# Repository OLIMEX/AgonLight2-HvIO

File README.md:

# AgonLight2-HvIO
High voltage optoisolated Four outputs and Four inputs and two Temperature sensor connectors for AgonLight2

https://www.olimex.com/Products/Retro-Computers/AgonLight2-HvIO/open-source-hardware

Features:

* AgonLight GPIO connector
* Four SSR relays 240VAC 1A
* Four optoisolated inputs 120-240VAC
* Two Dallas18B20 temperature sensors
* LED output indicators
* LED input indicators
* Power supply 3.3V and 5V LED indicators
* Dimensions 100x70mm

## Licenses

* Hardware is released under CERN Open Hardware Licence Version 2 - Strongly Reciprocal, all silkscreen credits to Olimex should remain;
* Software is released under GPL3 Licensee
* Documentation is released under CC BY-SA 4.0

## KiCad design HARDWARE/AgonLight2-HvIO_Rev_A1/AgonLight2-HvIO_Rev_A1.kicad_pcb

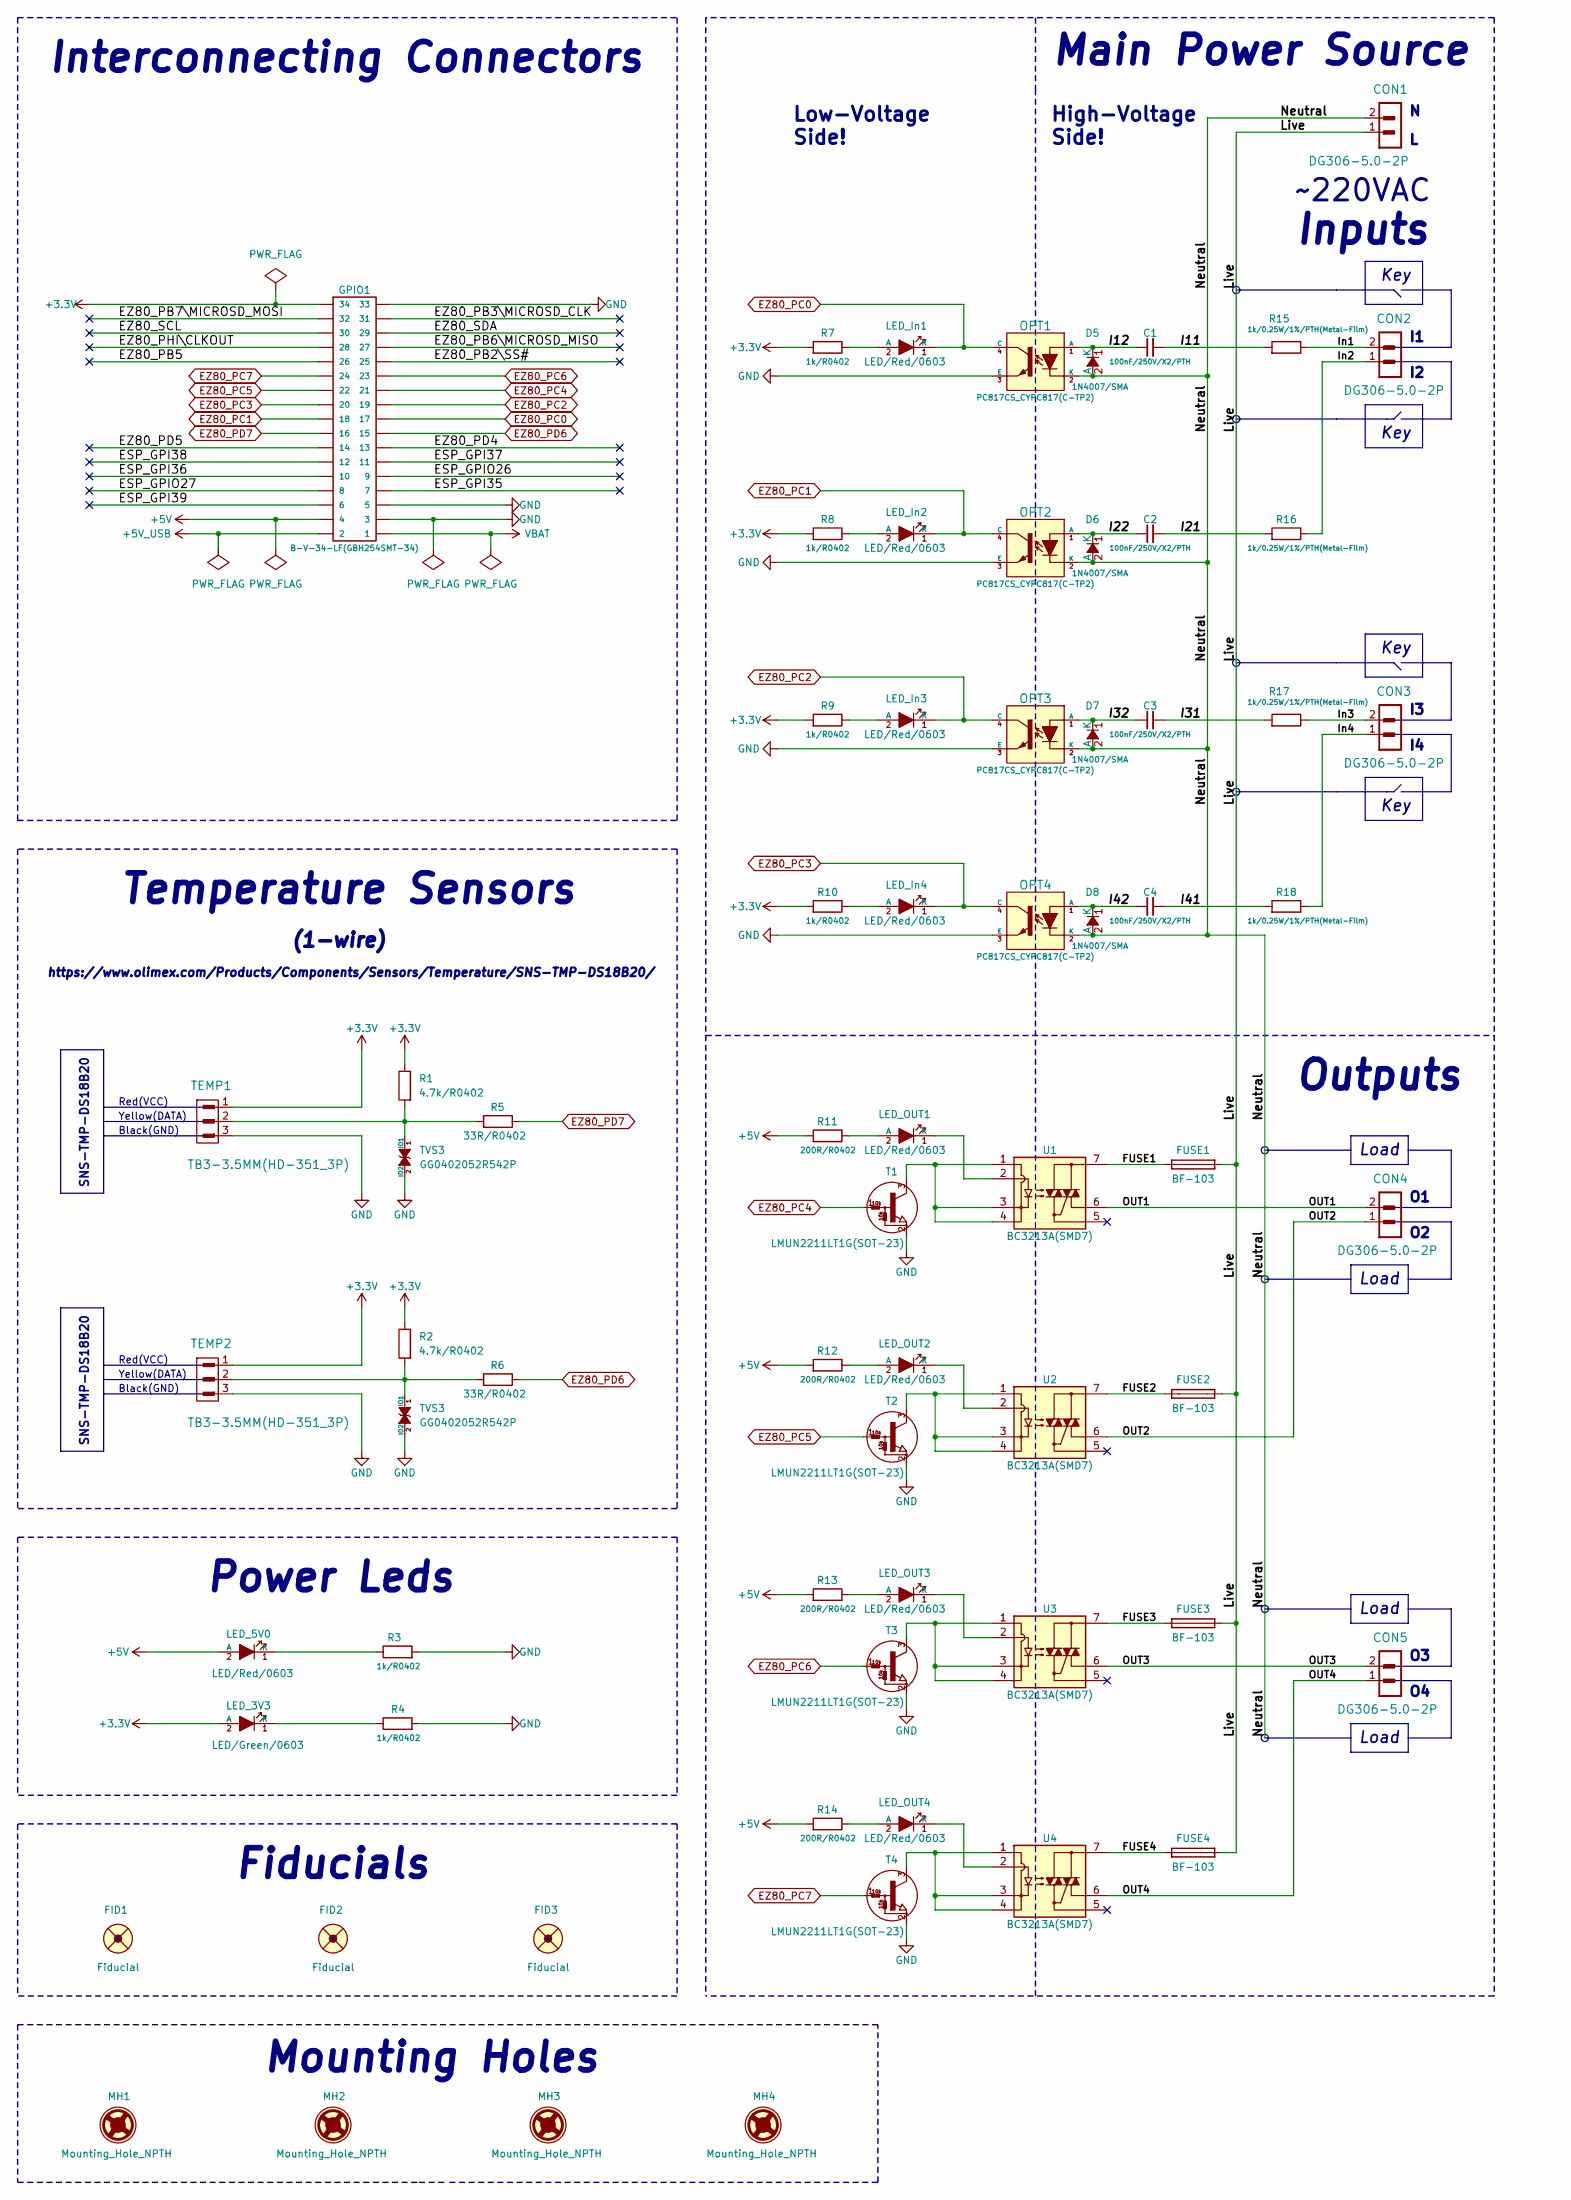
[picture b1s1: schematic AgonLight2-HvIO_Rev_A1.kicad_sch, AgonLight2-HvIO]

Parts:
C1, C2, C3, C4: 100nF/250V/X2/PTH; C600-700x250mils
CON1, CON2, CON3, CON4, CON5: DG306-5.0-2P; TB2-DG306-5.0_2P
D5, D6, D7, D8: 1N4007/SMA; SMA-KA
FID1, FID2, FID3: Fiducial; Fiducial1x3
FUSE1, FUSE2, FUSE3, FUSE4: BF-103; FUSE-HOLDER_BF-103
GPIO1: B-V-34-LF(GBH254SMT-34); GBH-254-SMT-34
LED_3V3: LED/Green/0603; LED_0603_KA
LED_5V0: LED/Red/0603; LED_0603_KA
LED_In1, LED_In2, LED_In3, LED_In4: LED/Red/0603; LED_0603_KA
LED_OUT1, LED_OUT2, LED_OUT3, LED_OUT4: LED/Red/0603; LED_0603_KA
MH1, MH2, MH3, MH4: Mounting_Hole_NPTH; Mounting_Hole_Drill-3.3mm_Clerance-7mm
OPT1, OPT2, OPT3, OPT4: PC817CS_CYPC817(C-TP2); H11A817C_SMD(PC817X3NIP06)_FP
R1, R2: 4.7k/R0402; R_0402_5MIL_DWS
R3, R4, R7, R8, R9, R10: 1k/R0402; R_0402_5MIL_DWS
R5, R6: 33R/R0402; R_0402_5MIL_DWS
R11, R12, R13, R14: 200R/R0402; R_0402_5MIL_DWS
R15, R16, R17, R18: 1k/0.25W/1%/PTH(Metal-Film); R_0.25W_PTH
T1, T2, T3, T4: LMUN2211LT1G(SOT-23); SOT23
TEMP1, TEMP2: TB3-3.5ММ(HD-351_3P); TB3-3.5mm
TVS3: GG0402052R542P; D_0402_5MIL_DWS
U1, U2, U3, U4: BC3213A(SMD7); SMD7_L9.70xW6.40_P2.54mm

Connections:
+3.3V: GPIO1.34, LED_3V3.2 (A), R1.1, R2.1, R7.2, R8.2, R9.2, R10.2, TEMP1.1, TEMP2.1
+5V: GPIO1.4, LED_5V0.2 (A), R11.2, R12.2, R13.2, R14.2
+5V_USB: GPIO1.2
/ESP_GPI35: GPIO1.7
/ESP_GPI36: GPIO1.10
/ESP_GPI37: GPIO1.11
/ESP_GPI38: GPIO1.12
/ESP_GPI39: GPIO1.6
/ESP_GPIO26: GPIO1.9
/ESP_GPIO27: GPIO1.8
/EZ80_PB2\SS#: GPIO1.25
/EZ80_PB3\MICROSD_CLK: GPIO1.31
/EZ80_PB5: GPIO1.26
/EZ80_PB6\MICROSD_MISO: GPIO1.27
/EZ80_PB7\MICROSD_MOSI: GPIO1.32
/EZ80_PD4: GPIO1.13
/EZ80_PD5: GPIO1.14
/EZ80_PHI\CLKOUT: GPIO1.28
/EZ80_SCL: GPIO1.30
/EZ80_SDA: GPIO1.29
/FUSE1: FUSE1.1, U1.7
/FUSE2: FUSE2.1, U2.7
/FUSE3: FUSE3.1, U3.7
/FUSE4: FUSE4.1, U4.7
/I11: C1.2, R15.2
/I12: C1.1, D5.1 (K), OPT1.1 (A)
/I21: C2.2, R16.2
/I22: C2.1, D6.1 (K), OPT2.1 (A)
/I31: C3.2, R17.2
/I32: C3.1, D7.1 (K), OPT3.1 (A)
/I41: C4.2, R18.2
/I42: C4.1, D8.1 (K), OPT4.1 (A)
/In1: CON2.2, R15.1
/In2: CON2.1, R16.1
/In3: CON3.2, R17.1
/In4: CON3.1, R18.1
/Live: CON1.1, FUSE1.2, FUSE2.2, FUSE3.2, FUSE4.2
/Neutral: CON1.2, D5.2 (A), D6.2 (A), D7.2 (A), D8.2 (A), OPT1.2 (K), OPT2.2 (K), OPT3.2 (K), OPT4.2 (K)
/OUT1: CON4.2, U1.6
/OUT2: CON4.1, U2.6
/OUT3: CON5.2, U3.6
/OUT4: CON5.1, U4.6
EZ80_PC0: GPIO1.17, LED_In1.1 (K), OPT1.4 (C)
EZ80_PC1: GPIO1.18, LED_In2.1 (K), OPT2.4 (C)
EZ80_PC2: GPIO1.19, LED_In3.1 (K), OPT3.4 (C)
EZ80_PC3: GPIO1.20, LED_In4.1 (K), OPT4.4 (C)
EZ80_PC4: GPIO1.21, T1.1 (B)
EZ80_PC5: GPIO1.22, T2.1 (B)
EZ80_PC6: GPIO1.23, T3.1 (B)
EZ80_PC7: GPIO1.24, T4.1 (B)
EZ80_PD6: GPIO1.15, R6.1
EZ80_PD7: GPIO1.16, R5.1
GND: GPIO1.3, GPIO1.5, GPIO1.33, OPT1.3 (E), OPT2.3 (E), OPT3.3 (E), OPT4.3 (E), R3.2, R4.2, T1.2 (E), T2.2 (E), T3.2 (E), T4.2 (E), TEMP1.3, TEMP2.3; also elsewhere on the board
unnamed: LED_3V3.1 (K), R4.1
unnamed: LED_5V0.1 (K), R3.1
unnamed: LED_In1.2 (A), R7.1
unnamed: LED_In2.2 (A), R8.1
unnamed: LED_In3.2 (A), R9.1
unnamed: LED_In4.2 (A), R10.1
unnamed: LED_OUT1.2 (A), R11.1
unnamed: LED_OUT1.1 (K), U1.2
unnamed: LED_OUT2.2 (A), R12.1
unnamed: LED_OUT2.1 (K), U2.2
unnamed: LED_OUT3.2 (A), R13.1
unnamed: LED_OUT3.1 (K), U3.2
unnamed: LED_OUT4.2 (A), R14.1
unnamed: LED_OUT4.1 (K), U4.2
unnamed: T1.3 (C), U1.1, U1.3, U1.4
unnamed: T2.3 (C), U2.1, U2.3, U2.4
unnamed: T3.3 (C), U3.1, U3.3, U3.4
unnamed: T4.3 (C), U4.1, U4.3, U4.4
unnamed 71: R1.2, R5.2, TEMP1.2; also elsewhere on the board
unnamed 72: R2.2, R6.2, TEMP2.2; also elsewhere on the board
VBAT: GPIO1.1

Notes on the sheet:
Key
Inputs
Mounting Holes
Load
Red(VCC)
SNS-TMP-DS18B20
Main Power Source
Black(GND)
Yellow(DATA)
Outputs
Low-Voltage Side!
Fiducials
https://www.olimex.com/Products/Components/Sensors/Temperature/SNS-TMP-DS18B20/
Power Leds
~220VAC
(1-wire)
High-Voltage Side!
Interconnecting Connectors
Temperature Sensors

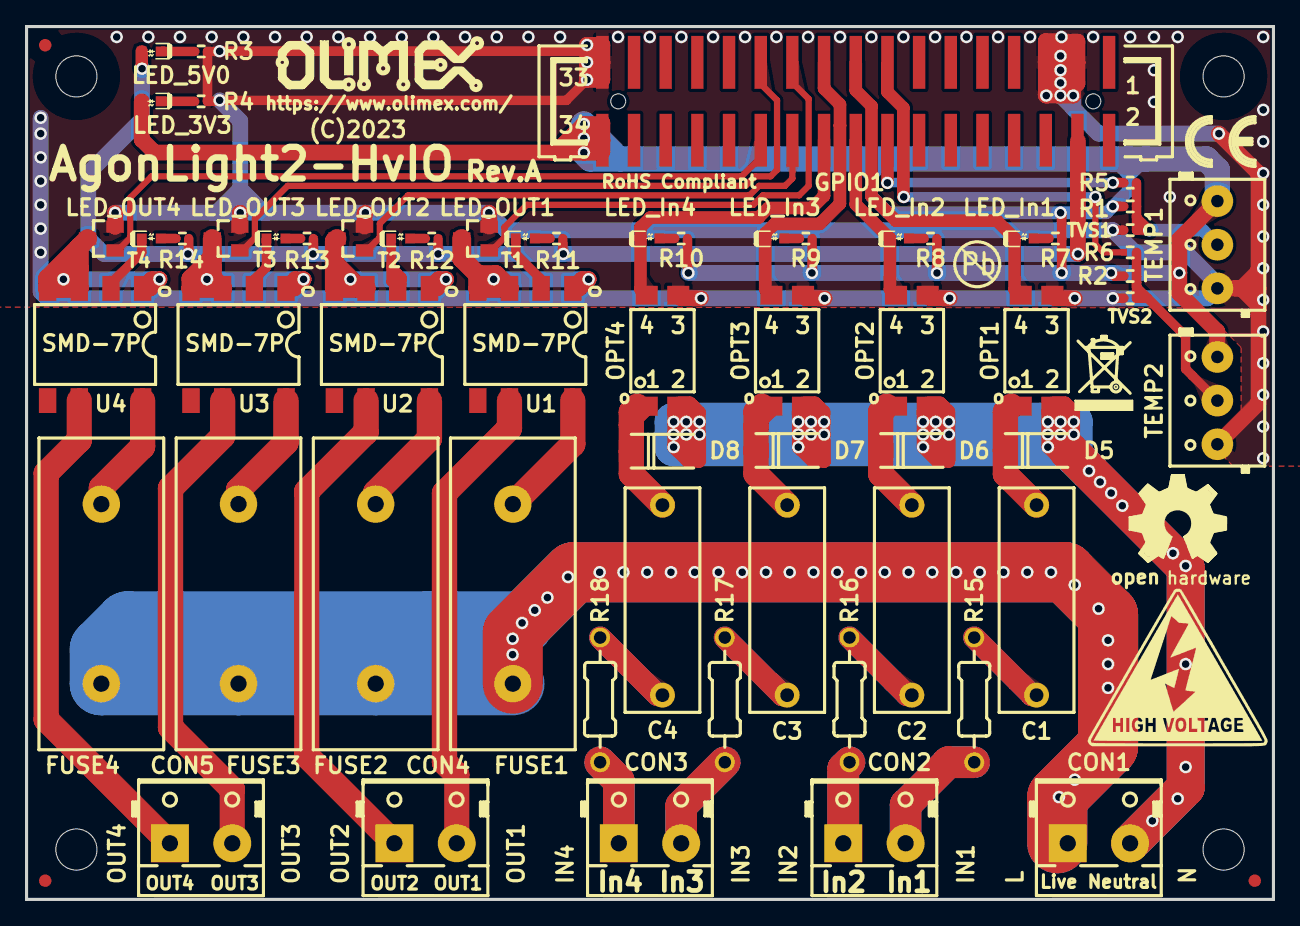
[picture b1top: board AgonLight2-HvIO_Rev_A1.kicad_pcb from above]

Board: 2 copper layers, 100.0 x 70.0 mm, 74 parts (0 on the bottom side), 55 nets.

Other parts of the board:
Logo_OLIMEX_TB: Logo_OLIMEX_TB
Sign_CE: CE_Sign
Sign_OSHW_8x8: Sign_OSHW_8x8
Sign_PB-Free: Sign_PB-Free
Sign_RecycleBin_1: Sign_RecycleBin_1
TVS1, TVS2: GG0402052R542P; D_0402_5MIL_DWS

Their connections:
GND: TVS1.2 (IO2), TVS2.2 (IO2); also elsewhere on the board
unnamed 71: TVS1.1 (IO1); also elsewhere on the board
unnamed 72: TVS2.1 (IO1); also elsewhere on the board

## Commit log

2023-10-04 user manual, cad files
2023-10-30 user manual update
2023-12-07 Update
    Revision A1

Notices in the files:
HARDWARE/AgonLight2-HvIO_Rev_A1/AgonLight2-HvIO_Rev_A1.kicad_pcb:
(C)2023
